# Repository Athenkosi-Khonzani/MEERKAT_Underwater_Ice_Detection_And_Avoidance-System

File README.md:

# MEERKAT — Underwater Ice Detection and Avoidance System

MEERKAT is a small, low-cost Autonomous Underwater Vehicle (AUV) designed to detect and avoid sub-surface ice (frazil ice, brash ice, and submerged keels of icebergs) in turbid polar waters. The platform descends and ascends using a **Variable Buoyancy System (VBS)** — a syringe driven by two DC motors — rather than thrusters, which keeps power consumption low and the acoustic signature small.

This repository contains the full design package: mechanical CAD, the power-electronics PCB, and the embedded firmware that runs the vehicle.

---

## System Architecture

MEERKAT is divided into four independent subsystems. Each lives in its own folder and has its own README with the wiring, build, and flashing details.

```
                      ┌──────────────────────────────┐
                      │      Surface ESP32           │
                      │  (mission start / telemetry) │
                      └──────────────┬───────────────┘
                                     │ UART (115200 8N1)
                                     │ JSON telemetry  /  "M:1" mission cmd
                ┌────────────────────┴────────────────────┐
                │   Control & Actuation Subsystem (F446)  │
                │   Mission state machine, motor PWM,     │
                │   VBS limit logic, battery monitoring   │
                └─┬──────────────┬──────────────┬─────────┘
                  │ I²C          │ UART         │ PWM
                  │              │              │
        ┌─────────▼────────┐ ┌───▼────────┐ ┌──▼───────────────┐
        │  INA219          │ │ DYP-L08    │ │ Dual DC motors   │
        │  (pack V / I)    │ │ Ultrasonic │ │ on VBS syringe   │
        └──────────────────┘ │ (obstacle) │ └──────────────────┘
                             └────────────┘
                  │ I²C
        ┌─────────▼────────────┐
        │  VL53L1X ToF         │
        │  (plunger position)  │
        └──────────────────────┘

        ┌──────────────────────┐    ┌──────────────────────┐
        │  Power Subsystem     │    │  Housing Subsystem   │
        │  3S Li-ion + TPS5430 │    │  Pressure vessel +   │
        │  → 5 V & 3V3 rails   │    │  motor / VBS mounts  │
        └──────────────────────┘    └──────────────────────┘
```

| Subsystem | What it does | Tech |
|---|---|---|
| **Control & Actuation** | Mission state machine; drives the VBS motors; reads sensors; speaks to the surface ESP32. | STM32F446RET6 (Nucleo-F446RE), STM32CubeIDE, HAL |
| **Sensory** | Stand-alone test firmware for the two ranging sensors used on the vehicle. | STM32F051C6T6, STM32CubeIDE, HAL |
| **Power** | 3S Li-ion pack regulated to a 5 V and a 3.3 V rail; INA219 pack monitor; SoC estimator firmware module. | KiCad 7, TPS5430DDAR buck regulators, INA219 |
| **Housing** | Watertight pressure vessel with separate compartments for the battery, two veroboards, and the syringe / motor assembly. | SolidWorks (`.SLDPRT`) |

---

## Mission Concept of Operations
 
1. **Surface idle.** Pack voltage is monitored. The vehicle waits for a `"M:1"` command from the surface ESP32 over UART3.
2. **Pre-descent check.** The plunger is forced to its minimum position (syringe empty of water). If the battery is below the warning threshold, the mission is refused.
3. **Descend.** The motor is driven forward through the H-bridge; the plunger is pushed out to its maximum position, the syringe pulls water in, and the vehicle sinks.
4. **Submerged loop.** The vehicle stays down for a configurable mission time. Throughout, it:
   * streams JSON telemetry to the surface every 500 ms (SoC, ToF, sonar, MCU temperature),
   * watches the upward-looking DYP-L08 ultrasonic for obstacles closer than 1 m,
   * watches the battery and aborts to ascent if SoC < 20 %.
5. **Ascend.** Once the mission timer expires *and* the path above is clear, the motor is driven in reverse through the H-bridge — the plunger is pulled back in, the syringe expels water, and the vehicle rises. If an obstacle is detected above, the ascent waits for it to clear.
The state machine is implemented in `Control And Actuation Subsystem/Control_System_2.0/Core/Src/main.c`.

---

## Repository Layout

```
.
├── Control And Actuation Subsystem/   # STM32CubeIDE project — main flight firmware
├── Sensory Subsystem/                 # STM32CubeIDE project — sensor bring-up firmware
├── Power Subsystem/                   # KiCad PCB project + SoC estimator source
└── Housing Subsystem/                 # SolidWorks part files for the pressure vessel
```

Each folder has its own README that covers wiring, build instructions, and any setup gotchas. Start there for hands-on work.

---

## Getting Started

### Firmware (Control & Sensory)
1. Install **STM32CubeIDE 1.13** or later.
2. `File → Open Projects from File System…` and point it at the `Control_System_2.0` or `Sensor_Test` folder.
3. Build (`Project → Build All`).
4. Connect the ST-Link, then `Run → Debug` to flash.

The Control subsystem expects a **one-shot calibration** the very first time it is flashed onto a new board — the procedure is documented in its README and is gated by an `#ifdef`-style block in `main.c`.

### PCB (Power)
1. Install **KiCad 7** or later.
2. Open `Power Subsystem/PCB/KHNATH002_Power_System/KHNATH002_Power_System.kicad_pro`.
3. The fabrication outputs for JLCPCB are under `jlcpcb/`.

### Mechanical (Housing)
The parts are `.SLDPRT` files for **SolidWorks 2022** or later. They have not yet been packaged into an assembly file — open each part individually.

---

## Status

| Subsystem | Hardware | Firmware | Verified end-to-end |
|---|:---:|:---:|:---:|
| Control & Actuation | ✅ | ✅ | ✅ |
| Sensory | ✅ | ✅ | ✅ |
| Power | ✅ | ✅ | ⚠️ bench-tested only |
| Housing | ✅ | n/a | ⚠️ dry-fit only |

---

## Authors

EEE4113F project, University of Cape Town, Department of Electrical Engineering.

* Athenkosi Khonzani — Power Subsystem 
* Ayanda Madlala — Housing Subsystem 
* Branden Nkhahle — Sensory Subsystem
* Manelisi Ngcobo — Control And Actuation Subsystem

---

## License

Unless otherwise noted, source code is provided as-is for academic use. STM32 HAL drivers are distributed under their original STMicroelectronics license (see `Drivers/` directory in each firmware project).

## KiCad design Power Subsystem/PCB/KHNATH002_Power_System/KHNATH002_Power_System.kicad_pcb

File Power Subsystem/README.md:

# MEERKAT AUV: Power Subsystem

## Overview
This subsystem is the **power-distribution and monitoring** layer of the MEERKAT AUV. It takes a 3-cell (3S) Li-ion battery pack and produces the two regulated rails the rest of the vehicle needs (**5 V** and **3.3 V**), while continuously measuring pack voltage and current so the flight firmware can estimate state of charge and abort the mission before the battery dies underwater.

The deliverable is two parts:

1. A **KiCad PCB project** (`PCB/KHNATH002_Power_System/`) implementing the regulators and the INA219 monitor.
2. A **portable C firmware module** (`SOC/`) — `battery.c`/`battery.h` — that runs on the flight MCU and turns INA219 readings into a usable SoC + runtime estimate.

---

## Hardware

### Battery Pack
* **Topology:** 3S Li-ion (three 18650-format cells in series).
* **Capacity:** 1000 mAh nominal (series cells share the pack mAh, they do not multiply).
* **Voltage range:**
  * Full = 3 × 4.20 V = **12.60 V**
  * Empty (cutoff) = 3 × 2.80 V ≈ **8.4 V** (configurable via `BAT_VOLTAGE_EMPTY_V`)

### Regulators (`TPS_Regulators.kicad_sch`)
Two **TPS5430DDAR** synchronous-buck regulators step the pack voltage down to the vehicle's two rails:

| Rail | Regulator | Loads |
|---|---|---|
| **5 V** | TPS5430DDAR | DC motors (via H-bridge driver), DYP-L08 ultrasonic sensor |
| **3.3 V** | TPS5430DDAR | STM32F446 MCU, VL53L1X ToF, INA219, ESP32 link |

The TPS5430 is rated 5.5–36 V in, 3 A continuous, with an internal high-side MOSFET — chosen for the headroom over the 12.6 V pack and for the relatively low BOM cost.

> **Note:** An earlier version of the design used the **MP2338GTL** (see `Regulators.kicad_sch`). That sheet is kept in the repo for history but is **not** part of the current top sheet (`KHNATH002_Power_System.kicad_sch`). The TPS implementation is the one that goes to fab.

### Monitoring (`Monitoring.kicad_sch`)
* **INA219** — high-side I²C current/voltage monitor sitting on the pack output, before the regulators. Configured for the 32 V bus-voltage range (the 16 V range saturates on a freshly charged 3S pack) and the /8 gain (320 mV full-scale on the shunt).
* **Shunt:** 0.1 Ω, giving a 100 µA current LSB after calibration → **CAL register = 4096**.
* **I²C address:** `0x40` (7-bit).

The INA219 talks to the flight MCU over **I²C1 (PB7 / PB8)** — see the Control & Actuation Subsystem README.

---

## PCB Layout

The KiCad project lives under:

```
Power Subsystem/PCB/KHNATH002_Power_System/
├── KHNATH002_Power_System.kicad_pro      # top-level project
├── KHNATH002_Power_System.kicad_sch      # top hierarchical sheet
├── KHNATH002_Power_System.kicad_pcb      # board layout
├── TPS_Regulators.kicad_sch              # 5V + 3V3 buck regulators (active)
├── Monitoring.kicad_sch                  # INA219 pack monitor
├── Regulators.kicad_sch                  # MP2338 regulators (legacy, unused)
└── jlcpcb/                               # fabrication outputs for JLCPCB
```

Open `KHNATH002_Power_System.kicad_pro` in **KiCad 7** or later.

---

## Firmware Module — `SOC/`

`battery.c` / `battery.h` is the on-board **State-of-Charge and runtime estimator**. It is not a stand-alone program — it links into the Control & Actuation Subsystem firmware (see that subsystem's README for how it is wired in).

### Algorithm
1. **Seed.** At init, read the open-circuit pack voltage (OCV) from the INA219 and map it through a lookup table to get the starting SoC. This compensates for the unknown charge state at power-on.
2. **Coulomb count.** Every `BAT_SAMPLE_PERIOD_MS` (default 500 ms), read voltage + current, then integrate current × Δt into a running `used_mAh` figure.
3. **OCV correction.** Resting-voltage measurements are blended into the coulomb-counted SoC slowly so the estimate self-corrects over time without jumping under load.
4. **Runtime.** Remaining mAh divided by recent-average current gives a live `runtime_sec` figure exposed via `Battery_GetData()`.

### Public API
```c
HAL_StatusTypeDef Battery_Init(I2C_HandleTypeDef *hi2c);
HAL_StatusTypeDef Battery_Update(void);
void              Battery_GetData(BatteryData_t *out);
void              Battery_RuntimeToHMS(uint32_t s, uint32_t *h, uint32_t *m, uint32_t *sec);
```

### `BatteryData_t` snapshot
```c
float   soc_pct;        // 0.0 – 100.0
float   voltage_V;      // pack terminal voltage
float   current_A;      // positive = discharging
float   used_mAh;       // since boot
float   remaining_mAh;
uint32_t runtime_sec;
BatteryStatus_t status; // OK / WARNING / CRITICAL
bool    valid;
```

### Configurable thresholds (in `battery.h`)
| Macro | Default | Meaning |
|---|---|---|
| `BAT_SERIES_CELLS` | 3 | Cells in series — adjust if pack changes. |
| `BAT_CAPACITY_MAH` | 1000 | Rated pack capacity (mAh). |
| `BAT_VOLTAGE_FULL_V` | 12.60 | Full pack voltage. |
| `BAT_VOLTAGE_EMPTY_V` | 8.40 | Cutoff. |
| `BAT_VDIV_RATIO` | 1.0 | Set to your divider ratio if INA219 V+ sees less than full pack voltage. |
| `BAT_SOC_OK_THRESHOLD` | 60 % | Above this → `BATTERY_OK`. |
| `BAT_SOC_WARNING_THRESHOLD` | 30 % | Above this → `BATTERY_WARNING`. Below → `BATTERY_CRITICAL`. |
| `BAT_SAMPLE_PERIOD_MS` | 500 | Coulomb-count integration period. |

The flight firmware uses these directly:
* SoC ≤ **30 %** → motor commands refused; pre-descent gate trips.
* SoC < **20 %** → in-mission abort; vehicle ascends if the path is clear.

---

## Build & Flash (firmware module)
The module is built as part of the Control & Actuation Subsystem firmware. To use it stand-alone in another project:

1. Copy `SOC/battery.c` and `SOC/battery.h` into your project.
2. Include `"battery.h"` in your `main.c`.
3. After your I²C peripheral is initialised, call `Battery_Init(&hi2c1)`.
4. Call `Battery_Update()` in your main loop (it rate-limits itself internally).
5. Read data with `Battery_GetData(&snapshot)`.

The module depends only on the STM32 HAL I²C driver — no other RTOS or library.

---

## Voltage-Divider Note (read this before powering up)

The INA219's bus-voltage input is rated to 26 V max but its 16 V config-register mode saturates above ~16 V. The 3S pack peaks at 12.6 V, which is well inside the 26 V hardware limit — **so this design connects V+ directly to the pack**, and `BAT_VDIV_RATIO` is set to `1.0`.

If you re-spin the board with a divider (e.g. for a 4S pack), update `BAT_VDIV_RATIO` in `battery.h` to the new divider ratio so the firmware un-scales the reading correctly.

---

## Status & Known Issues
* The TPS5430 layout has been verified on the bench but **not yet integrated under load with the full vehicle**.
* `Regulators.kicad_sch` (MP2338 variant) is kept in the repo for history. It is **not** part of the current build.
* The schematic does not yet include explicit reverse-polarity protection on the battery input — a Schottky or P-FET is recommended for the next revision.

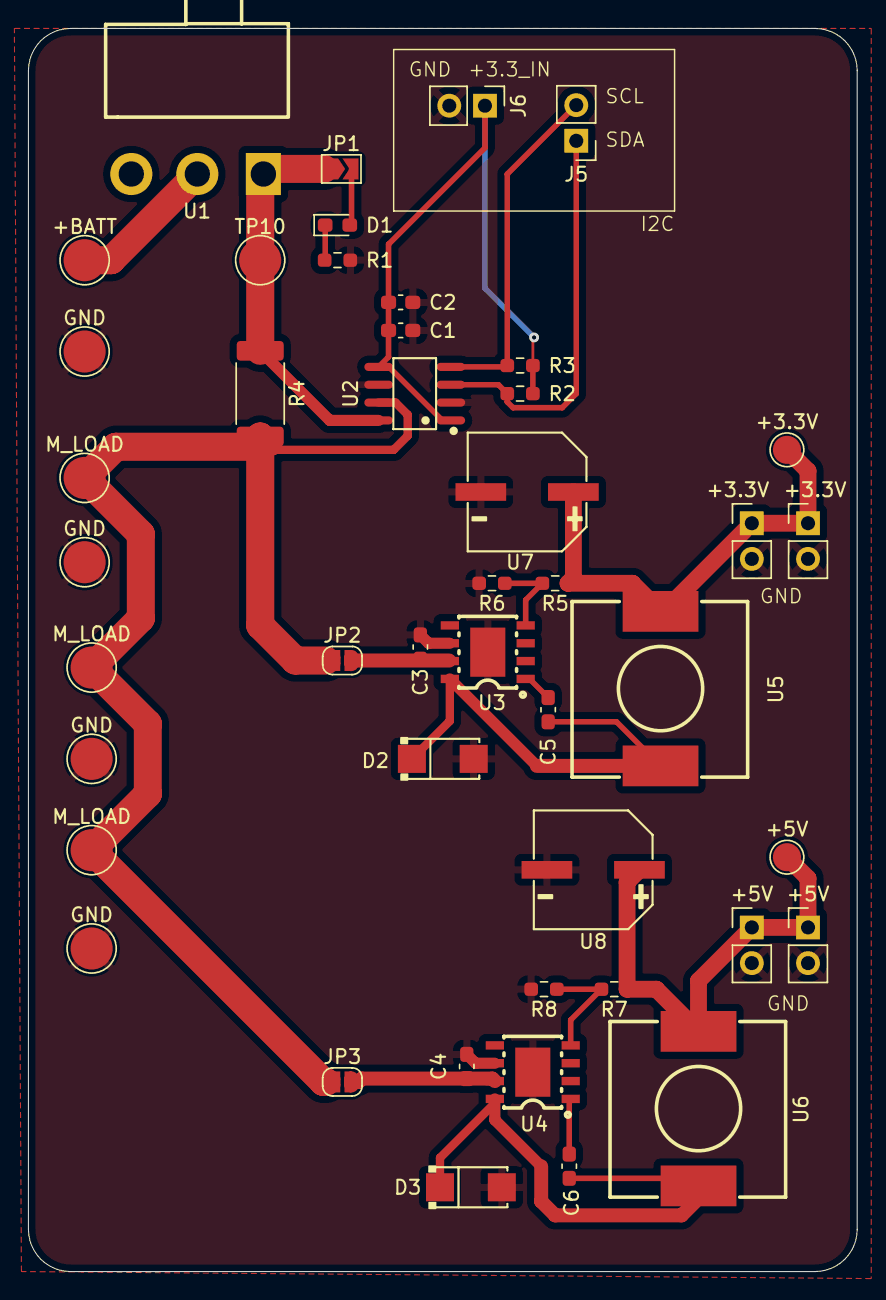
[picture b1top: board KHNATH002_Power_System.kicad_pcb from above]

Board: 2 copper layers, 59.0 x 88.5 mm, 45 parts (0 on the bottom side), 19 nets.

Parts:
+3.3V: +3.3V; TestPoint_Pad_D2.0mm
+3.3V#2, +3.3V#3, +5V#2, +5V#3: Conn_01x02_Pin; PinHeader_1x02_P2.54mm_Vertical
+5V: +5V; TestPoint_Pad_D2.0mm
+BATT: +BATT; TestPoint_Pad_D3.0mm
C1, C3, C4: 10u; C_0603_1608Metric_Pad1.08x0.95mm_HandSolder
C2: 0.1u; C_0603_1608Metric_Pad1.08x0.95mm_HandSolder
C5, C6: 0.01u; C_0603_1608Metric_Pad1.08x0.95mm_HandSolder
D1: LED; LED_0603_1608Metric_Pad1.05x0.95mm_HandSolder
D2, D3: B340A; SMA_L4.3-W2.6-LS5.1-RD
GND: GND; TestPoint_Pad_D3.0mm
GND#2, GND#3, GND#4: GND; TestPoint_Pad_D3.0mm
J5, J6: Conn_01x02_Pin; PinHeader_1x02_P2.54mm_Vertical
JP1: Jumper_2_Open; SolderJumper-2_P1.3mm_Open_TrianglePad1.0x1.5mm
JP2, JP3: Jumper_2_Open; SolderJumper-2_P1.3mm_Open_RoundedPad1.0x1.5mm
M_LOAD: LOAD; TestPoint_Pad_D3.0mm
M_LOAD#2, M_LOAD#3: LOAD; TestPoint_Pad_D3.0mm
R1, R7: 10k; R_0603_1608Metric_Pad0.98x0.95mm_HandSolder
R2, R3: 4.7k; R_0603_1608Metric_Pad0.98x0.95mm_HandSolder
R4: 2m; R_2512_6332Metric_Pad1.40x3.35mm_HandSolder
R5: 20k; R_0603_1608Metric_Pad0.98x0.95mm_HandSolder
R6: 12k; R_0603_1608Metric_Pad0.98x0.95mm_HandSolder
R8: 3.3k; R_0603_1608Metric_Pad0.98x0.95mm_HandSolder
TP10: +12V; TestPoint_Pad_D3.0mm
U1: SS-12D06L5; SW-TH_3P-P4.70_L11.1-W12.7
U2: INA219AIDR; SOIC-8_L4.9-W3.9-P1.27-LS6.0-BL
U3, U4: TPS5430DDAR; ESOP-8_L4.9-W3.9-P1.27-LS6.0-TL-EP
U5, U6: SMDRI127-150MT; IND-SMD_L12.5-W12.5_RLF12545T
U7, U8: RVT1V221M0810; CAP-SMD_BD8.0-L8.3-W8.3-LS9.1-FD

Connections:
+3.3V: +3.3V.1, +3.3V#2.1, +3.3V#3.1, R5.1, U5.1, U7.1
+5V: +5V.1, +5V#2.1, +5V#3.1, R7.1, U6.1, U8.1
+12V: JP1.1 (A), R4.1, TP10.1, U1.1, U2.8 (VIN+)
+BATT: +BATT.1, U1.2
/Monitoring/+3.3_IN: C1.1, C2.1, J6.1, R2.1, R3.1, U2.1 (A1), U2.5 (VS)
/TPS_Regulators/BOOT_3.3: C5.2, U3.1 (BOOT)
/TPS_Regulators/BOOT_5: C6.2, U4.1 (BOOT)
/TPS_Regulators/PH_3.3: C5.1, D2.1 (K), U3.8 (PH), U5.2
/TPS_Regulators/PH_5: C6.1, D3.1 (K), U4.8 (PH), U6.2
/TPS_Regulators/VIN_3.3: C3.1, JP2.2 (B), U3.7 (VIN)
/TPS_Regulators/VIN_5: C4.1, JP3.2 (B), U4.7 (VIN)
/TPS_Regulators/VS_3.3: R5.2, R6.1, U3.4 (VSENSE)
/TPS_Regulators/VS_5: R7.2, R8.1, U4.4 (VSENSE)
GND: +3.3V#2.2, +3.3V#3.2, +5V#2.2, +5V#3.2, C1.2, C2.2, C3.2, C4.2, D2.2 (A), D3.2 (A), GND.1, GND#2.1, GND#3.1, GND#4.1, J6.2, R1.2, R6.2, R8.2, U2.2 (A0), U2.6 (GND), U3.6 (GND), U3.9 (PowerPAD), U4.6 (GND), U4.9 (PowerPAD), U7.2, U8.2
LOAD: JP2.1 (A), JP3.1 (A), M_LOAD.1, M_LOAD#2.1, M_LOAD#3.1, R4.2, U2.7 (VIN-)
unnamed: D1.2 (A), JP1.2 (B)
unnamed: D1.1 (K), R1.1
SCL: J5.2, R3.2, U2.4 (SCL)
SDA: J5.1, R2.2, U2.3 (SDA)

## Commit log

2026-05-18 Ground works
2026-05-18 Added SOC files
2026-05-18 Add README for Sensory Subsystem firmware
    This README provides an overview of the Sensory Subsystem firmware for the MEERKAT AUV, detailing sensor integration, hardware configuration, and core file structure.
2026-05-18 Revise README with updated sensor information
    Updated sensor specifications and calibration details in the README.
2026-05-22 Full Control filed upload
2026-05-22 Sensor files extracted
2026-05-22 Created README.md for MEERKAT project
    Add README for MEERKAT underwater ice detection AUV
2026-05-22 Revise README with updated authors and project info
    Updated authors and project details in README.
2026-05-22 Created README for Power Subsystem
    Add detailed documentation for the Power Subsystem, including hardware specifications, PCB layout, and firmware module information.
2026-05-22 Added README for Control & Actuation Subsystem firmware
    Added detailed README for Control & Actuation Subsystem firmware, including overview, hardware configuration, mission state machine, core file structure, calibration instructions, and troubleshooting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
2026-05-22 Added README for Housing Subsystem
    Added detailed README for Housing Subsystem including overview, parts, internal layout, sealing strategy, manufacturing notes, file opening instructions, and status.
2026-05-22 Updated README with system architecture and operations
